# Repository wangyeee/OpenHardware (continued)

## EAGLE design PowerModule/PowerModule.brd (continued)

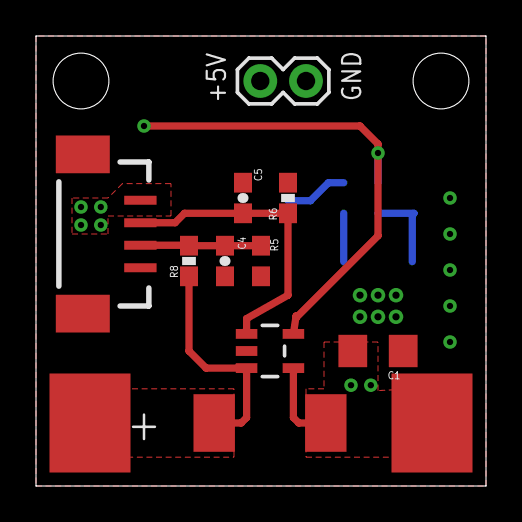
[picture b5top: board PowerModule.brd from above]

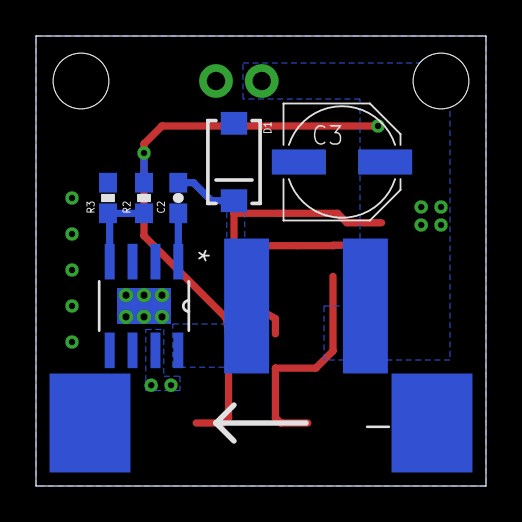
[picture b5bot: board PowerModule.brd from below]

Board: 2 copper layers, 25.0 x 25.0 mm, 21 parts (9 on the bottom side), 9 nets.

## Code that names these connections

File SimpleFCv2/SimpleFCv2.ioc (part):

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Mcu.Name=STM32F405RGTx
Mcu.Package=LQFP64
Mcu.UserName=STM32F405RGTx
PA0-WKUP.GPIOParameters=GPIO_Label
PA0-WKUP.GPIO_Label=RC2_INVT
PA0-WKUP.Mode=Asynchronous
PA0-WKUP.Signal=UART4_TX
PA1.Mode=Asynchronous
PA1.Signal=UART4_RX
PA10.Mode=Asynchronous
PA10.Signal=USART1_RX
PA11.Mode=Device_Only
PA11.Signal=USB_OTG_FS_DM
PA12.Mode=Device_Only
PA12.Signal=USB_OTG_FS_DP
PA13.Mode=JTAG_4_pins
PA13.Signal=SYS_JTMS-SWDIO
PA14.Mode=JTAG_4_pins
PA14.Signal=SYS_JTCK-SWCLK
PA15.Mode=JTAG_4_pins
PA15.Signal=SYS_JTDI
PA2.GPIOParameters=GPIO_Label
PA2.GPIO_Label=RC1_INVT
PA2.Mode=Asynchronous
PA2.Signal=USART2_TX
PA3.Mode=Asynchronous
PA3.Signal=USART2_RX
PA4.GPIOParameters=GPIO_Label
PA4.GPIO_Label=BARO_CS
PA4.Signal=GPIO_Output
PA5.Mode=Full_Duplex_Master
PA5.Signal=SPI1_SCK
PA6.Mode=Full_Duplex_Master
PA6.Signal=SPI1_MISO
PA7.Mode=Full_Duplex_Master
PA7.Signal=SPI1_MOSI
PA8.GPIOParameters=GPIO_Label
PA8.GPIO_Label=SD_DECT
PA8.Signal=GPXTI8
PA9.Mode=Asynchronous
PA9.Signal=USART1_TX
PB0.Signal=S_TIM3_CH3
PB1.Signal=S_TIM3_CH4
PB10.Mode=Asynchronous
PB10.Signal=USART3_TX
PB11.Mode=Asynchronous
PB11.Signal=USART3_RX
PB12.Mode=Slave
PB12.Signal=CAN2_RX
PB13.Mode=Slave
PB13.Signal=CAN2_TX
PB14.Signal=S_TIM12_CH1
PB15.Signal=S_TIM12_CH2
PB2.GPIOParameters=GPIO_Label
PB2.GPIO_Label=BOOT1
PB2.Signal=GPIO_Input
PB3.Mode=JTAG_4_pins
PB3.Signal=SYS_JTDO-SWO
PB4.GPIOParameters=GPIO_Label
PB4.GPIO_Label=LED3
PB4.Signal=GPIO_Output
PB5.GPIOParameters=GPIO_Label
PB5.GPIO_Label=LED4
PB5.Signal=GPIO_Output
PB6.Mode=I2C
PB6.Signal=I2C1_SCL
PB7.Mode=I2C
PB7.Signal=I2C1_SDA
PB8.Signal=S_TIM4_CH3
PB9.Signal=S_TIM4_CH4
PC0.Signal=ADCx_IN10
PC1.Signal=ADCx_IN11
PC10.Mode=SD_4_bits_Wide_bus
PC10.Signal=SDIO_D2
PC11.Mode=SD_4_bits_Wide_bus
PC11.Signal=SDIO_D3
PC12.Mode=SD_4_bits_Wide_bus
PC12.Signal=SDIO_CK
PC13-ANTI_TAMP.GPIOParameters=GPIO_Label
PC13-ANTI_TAMP.GPIO_Label=MPU_INT
PC13-ANTI_TAMP.Signal=GPXTI13
PC14-OSC32_IN.GPIOParameters=GPIO_Label
PC14-OSC32_IN.GPIO_Label=LED2
PC14-OSC32_IN.Signal=GPIO_Output
PC15-OSC32_OUT.GPIOParameters=GPIO_Label
PC15-OSC32_OUT.GPIO_Label=LED1
PC15-OSC32_OUT.Signal=GPIO_Output
PC2.Signal=ADCx_IN12
PC3.Signal=ADCx_IN13
PC4.GPIOParameters=GPIO_Label
PC4.GPIO_Label=MPU_CS
PC4.Signal=GPIO_Output
PC5.GPIOParameters=GPIO_Label
PC5.GPIO_Label=MAG_INT
PC5.Signal=GPXTI5
PC6.Signal=S_TIM3_CH1
PC7.Signal=S_TIM3_CH2
PC8.Mode=SD_4_bits_Wide_bus
PC8.Signal=SDIO_D0
PC9.Mode=SD_4_bits_Wide_bus
PC9.Signal=SDIO_D1
PD2.Mode=SD_4_bits_Wide_bus
PD2.Signal=SDIO_CMD
PH0-OSC_IN.Mode=HSE-External-Clock-Source
PH0-OSC_IN.Signal=RCC_OSC_IN
PH1-OSC_OUT.Mode=HSE-External-Clock-Source
PH1-OSC_OUT.Signal=RCC_OSC_OUT
RCC.HSE_VALUE=25000000
RCC.SYSCLKFreq_VALUE=168000000
RCC.SYSCLKSource=RCC_SYSCLKSOURCE_PLLCLK

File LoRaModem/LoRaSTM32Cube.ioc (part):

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Mcu.Name=STM32F103C(8-B)Tx
Mcu.Package=LQFP48
Mcu.UserName=STM32F103CBTx
PA1.Signal=GPIO_Output
PA10.Mode=Asynchronous
PA10.Signal=USART1_RX
PA13.Mode=Trace_Asynchronous_SW
PA13.Signal=SYS_JTMS-SWDIO
PA14.Mode=Trace_Asynchronous_SW
PA14.Signal=SYS_JTCK-SWCLK
PA2.Mode=Half_duplex(single_wire_mode)
PA2.Signal=USART2_TX
PA3.Signal=GPXTI3
PA4.Signal=GPIO_Output
PA5.Mode=Full_Duplex_Master
PA5.Signal=SPI1_SCK
PA6.Mode=Full_Duplex_Master
PA6.Signal=SPI1_MISO
PA7.Mode=Full_Duplex_Master
PA7.Signal=SPI1_MOSI
PA8.Signal=GPIO_Output
PA9.Mode=Asynchronous
PA9.Signal=USART1_TX
PB0.Signal=GPIO_Output
PB12.Signal=GPIO_Output
PB13.Mode=Full_Duplex_Master
PB13.Signal=SPI2_SCK
PB14.Mode=Full_Duplex_Master
PB14.Signal=SPI2_MISO
PB15.Mode=Full_Duplex_Master
PB15.Signal=SPI2_MOSI
PB3.Mode=Trace_Asynchronous_SW
PB3.Signal=SYS_JTDO-TRACESWO
PB6.Signal=S_TIM4_CH1
PB7.Signal=S_TIM4_CH2
PB8.Mode=Master
PB8.Signal=CAN_RX
PB9.Mode=Master
PB9.Signal=CAN_TX
PD0-OSC_IN.Mode=HSE-External-Oscillator
PD0-OSC_IN.Signal=RCC_OSC_IN
PD1-OSC_OUT.Mode=HSE-External-Oscillator
PD1-OSC_OUT.Signal=RCC_OSC_OUT
RCC.SYSCLKFreq_VALUE=48000000
RCC.SYSCLKSource=RCC_SYSCLKSOURCE_PLLCLK

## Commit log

2016-02-22 Initial version. Including PowerModule and SerialBTBridge.
2016-02-28 Add multi rotor hub design files.
2016-06-13 Add ACS758 current sensor board.
2018-08-31 Add SimpleFC design files.
2018-09-28 Add design files for LoRa Modem.
2018-09-28 Add PDF schematics.
2018-09-28 Create LICENSE
2018-10-03 Add design files for TinyFC core board.
2018-10-07 Add design files for oscillator breakout board.
2018-10-07 Add 3D render for SimpleFC.
2018-10-09 Add description for each folder.
2018-10-27 Add files for ReflowOvenController
2019-01-03 Add STM32CubeMX design file for SimpleFC
2019-04-05 Import project AirSensor
2019-04-05 Add readme for AirSensor
2019-04-05 Update readme of AirSensor
2019-05-01 Add DIYDummyLoad EAGLE files
2019-05-01 Update README for DIYDummyLoad
2019-05-15 1. Replace SWD connector with 10 pin SMD 2x5 connector in AirSensor. 2. Add signal name silk screen in AirSensor.
2019-05-15 Update schematics and PCB print for AirSensor.
2019-05-17 Add version 2 of SimpleFC
2019-05-17 Add SimpleFCv2 schematics print and update README
2019-05-18 Replace MAG3110 with MMC5883MA in SimpleFC
2019-05-18 Update SimpleFCv2 README
2019-05-18 Update gitignore to include gerber drill files
2019-05-27 Add design files for TinyBEC
2019-05-27 Update README for TinyBEC
2019-06-04 Add design files for SimpleFCv2 with integrated GPS receiver
2019-06-04 Update README for SimpleFC_G
2020-01-29 Refactor SimpleFC schematics with latest KiCAD libraries.
